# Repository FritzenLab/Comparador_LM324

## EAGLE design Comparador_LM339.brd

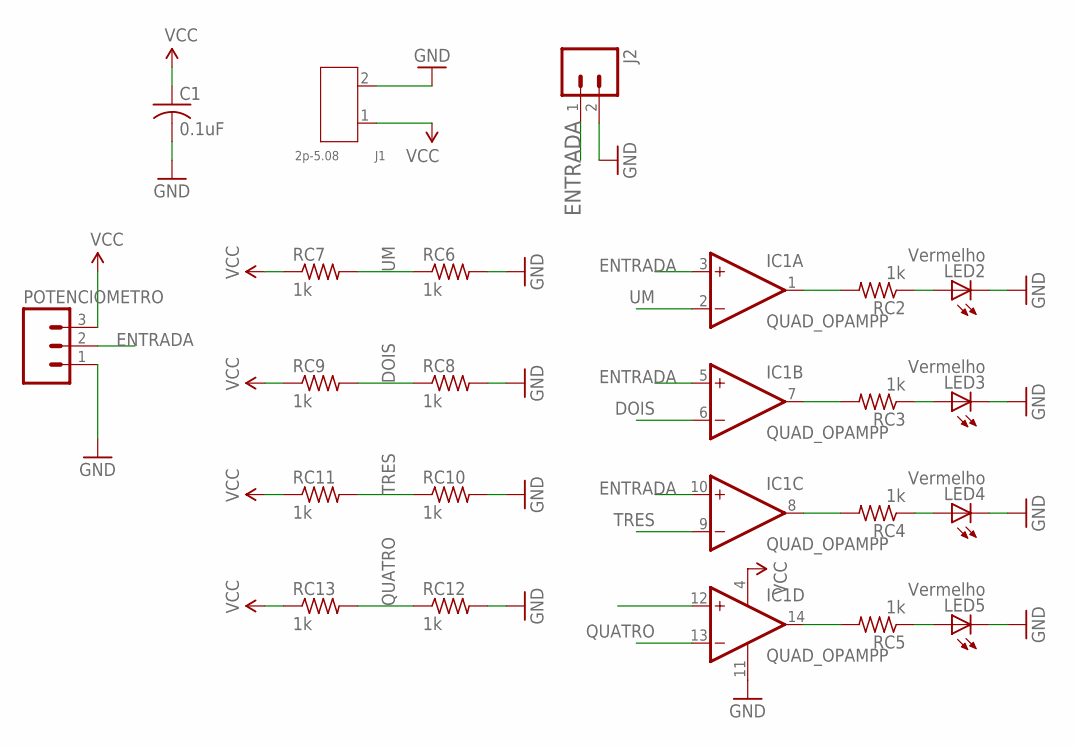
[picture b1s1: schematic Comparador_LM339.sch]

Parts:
C1: 0.1uF; C050-024X044
IC1: QUAD_OPAMPP; DIL14
J1: 2p-5.08; H2-5.0-10.5X8.0MM
J2: M02PTH; 1X02
LED2, LED3, LED4, LED5: Vermelho; LED5MM
POTENCIOMETRO: M03-SCREW-5MM; SCREWTERMINAL-5MM-3
RC2, RC3, RC4, RC5, RC6, RC7, RC8, RC9, RC10, RC11, RC12, RC13: 1k; 0207/10

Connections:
DOIS: IC1.6 (-IN), RC8.1, RC9.2
ENTRADA: IC1.3 (+IN), IC1.5 (+IN), IC1.10 (+IN), IC1.12 (+IN), J2.1, POTENCIOMETRO.2
GND: C1.2, IC1.11 (V-), J1.2, J2.2, LED2.K (C), LED3.K (C), LED4.K (C), LED5.K (C), POTENCIOMETRO.1, RC6.2, RC8.2, RC10.2, RC12.2
unnamed: IC1.1 (OUT), RC2.2
unnamed: IC1.7 (OUT), RC3.2
unnamed: IC1.8 (OUT), RC4.2
unnamed: IC1.14 (OUT), RC5.2
unnamed: LED2.A, RC2.1
unnamed: LED3.A, RC3.1
unnamed: LED4.A, RC4.1
unnamed: LED5.A, RC5.1
QUATRO: IC1.13 (-IN), RC12.1, RC13.2
TRES: IC1.9 (-IN), RC10.1, RC11.2
UM: IC1.2 (-IN), RC6.1, RC7.2
VCC: C1.1, IC1.4 (V+), J1.1, POTENCIOMETRO.3, RC7.1, RC9.1, RC11.1, RC13.1

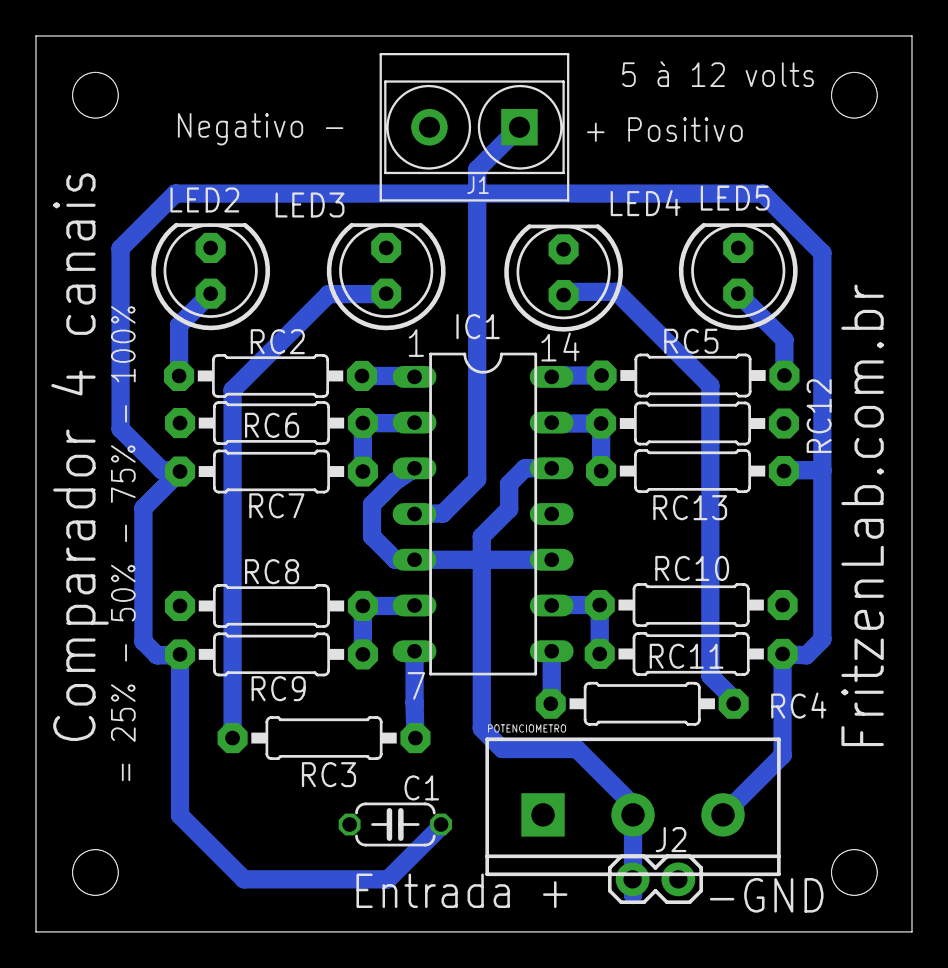
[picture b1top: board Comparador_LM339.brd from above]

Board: 2 copper layers, 48.7 x 49.8 mm, 21 parts (0 on the bottom side), 15 nets.

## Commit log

2016-05-04 Primeiro upload de arquivos
    Placa "comparador LM324", um circuito comparador de nível com entrada
    para potenciômetro ou externo (conector), comparando a entrada com 4
    níveis diferentes: 25, 50, 75 e 100% e acendendo um led para cada nível.

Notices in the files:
parts and their libraries:
SparkFun-Connectors: Licensing: Creative Commons ShareAlike 4.0 International - https://creativecommons.org/licenses/by-sa/4.0
